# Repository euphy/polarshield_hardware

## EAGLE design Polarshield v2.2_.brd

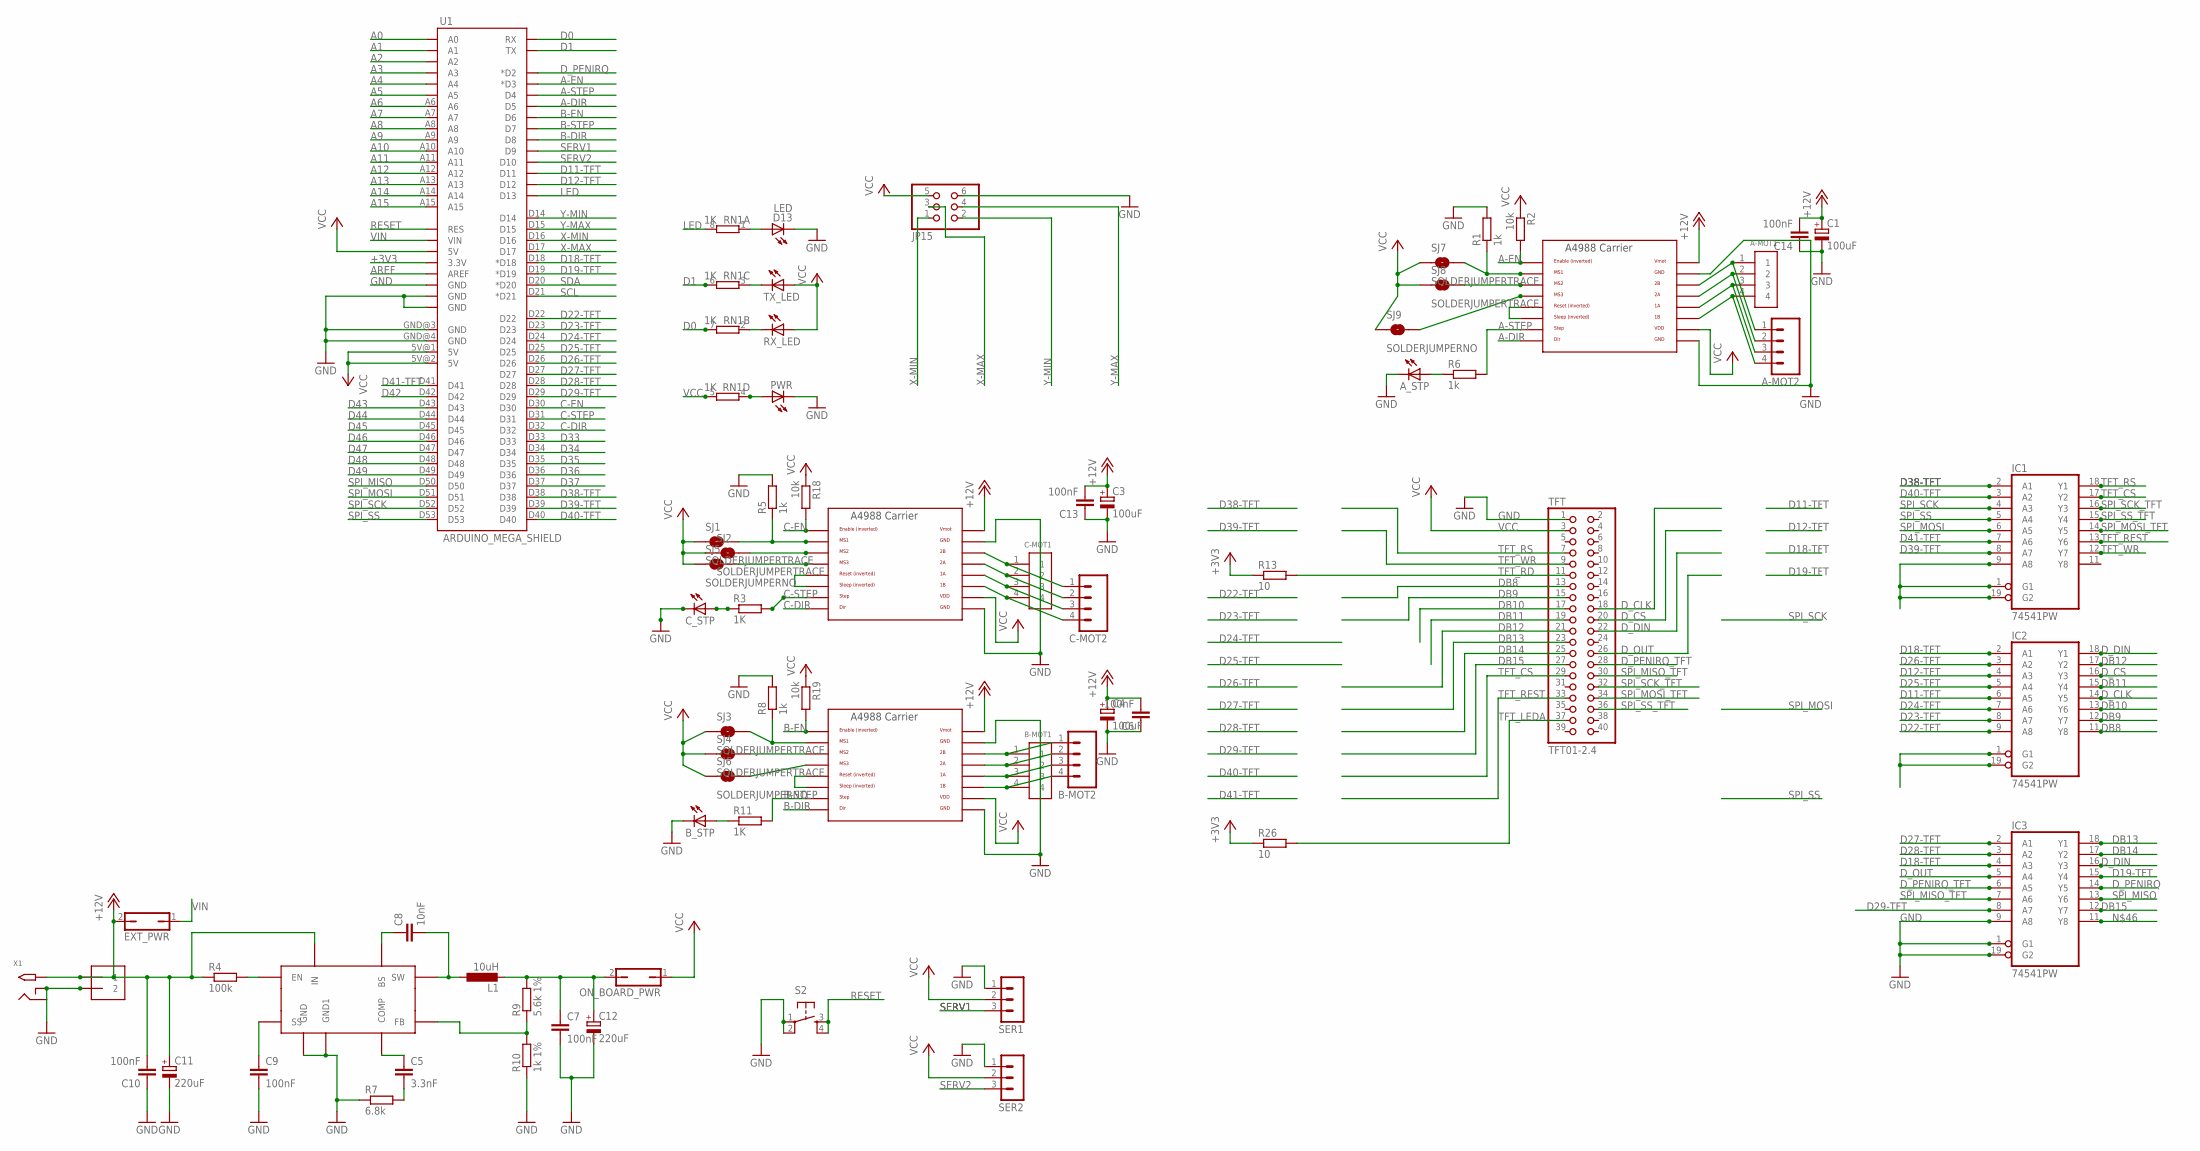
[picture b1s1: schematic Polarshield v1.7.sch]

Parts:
A-MOT1: 1X4-BIG; 1X04-BIG
A-MOT2: M04SCREW; SCREWTERMINAL-3.5MM-4
A_STP: LEDCHIP-LED0805; CHIP-LED0805
B-MOT1: 1X4-BIG; 1X04-BIG
B-MOT2: M04SCREW; SCREWTERMINAL-3.5MM-4
B_STP: LEDCHIP-LED0805; CHIP-LED0805
C1, C3, C4: 100uF; 153CLV-0605
C5: 3.3nF; C0805K
C6, C13, C14: 100nF; C0805
C7, C9, C10: 100nF; C0805K
C8: 10nF; C0805K
C11, C12: 220uF; 153CLV-0807
C-MOT1: 1X4-BIG; 1X04-BIG
C-MOT2: M04SCREW; SCREWTERMINAL-3.5MM-4
C_STP: LEDCHIP-LED0805; CHIP-LED0805
D13: LED; CHIP-LED0805
EXT_PWR: JP1Q; JP1
IC1, IC2, IC3: 74541PW; TSSOP20
IC4: MP2307; SOIC8
J1: 1X2-3.5MM
JP15: PINHD-2X3; 2X03
L1: 10uH; PIS2816
ON_BOARD_PWR: JP1Q; JP1
PWR: LEDCHIP-LED0805; CHIP-LED0805
R1, R5, R6, R8: 1k; R0805
R2, R18, R19: 10k; R0805
R3, R11: 1K; R0805
R4: 100k; R0805
R7: 6.8k; R0805
R9: 5.6k 1%; R0805
R10: 1k 1%; R0805
R13, R26: 10; R0805
RN1: 1K; EXBS8V
RX_LED: LEDCHIP-LED0805; CHIP-LED0805
S2: TAC_SWITCHPTH; TACTILE-PTH
SER1, SER2: 3PIN-HEADER
SJ1, SJ2, SJ3, SJ4, SJ7, SJ8: SOLDERJUMPERTRACE; SJ_2S-TRACE
SJ5, SJ6, SJ9: SOLDERJUMPERNO; SJ_2S-NO
TFT: TFT01-2.4
TX_LED: LEDCHIP-LED0805; CHIP-LED0805
U1: ARDUINO_MEGA_SHIELD
U$1, U$6, U$7: A4988BREAKOUT
X1: 2.1MMJACKTHM; PJ-102A

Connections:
+12V: C1.+, C3.+, C4.+, C6.2, C10.2, C11.+, C13.2, C14.2, EXT_PWR.2, IC4.IN, J1.1, R4.1, U$1.VMOT, U$6.VMOT, U$7.VMOT, X1.TIP; also elsewhere on the board
A0: U1.A0; also elsewhere on the board
A1: U1.A1; also elsewhere on the board
A2: U1.A2; also elsewhere on the board
A3: U1.A3; also elsewhere on the board
A4: U1.A4; also elsewhere on the board
A5: U1.A5; also elsewhere on the board
A6: U1.A6; also elsewhere on the board
A7: U1.A7; also elsewhere on the board
A8: U1.A8; also elsewhere on the board
A9: U1.A9; also elsewhere on the board
A10: U1.A10; also elsewhere on the board
A11: U1.A11; also elsewhere on the board
A12: U1.A12; also elsewhere on the board
A13: U1.A13; also elsewhere on the board
A14: U1.A14; also elsewhere on the board
A15: U1.A15; also elsewhere on the board
A-DIR: U1.D5, U$1.DIR
A-EN: R2.2, U1.D3 (*D3), U$1.EN
A-STEP: R6.2, U1.D4, U$1.STEP
AREF: U1.AREF
B-DIR: U1.D8, U$7.DIR
B-EN: R19.2, U1.D6, U$7.EN
B-STEP: R11.2, U1.D7, U$7.STEP
C-DIR: U1.D32, U$6.DIR
C-EN: R18.2, U1.D30, U$6.EN
C-STEP: R3.2, U1.D31, U$6.STEP
D0: RN1.7 (2), U1.RX
D1: RN1.6 (2), U1.TX
D11-TFT: IC2.6 (A5), U1.D11
D12-TFT: IC2.4 (A3), U1.D12
D19-TFT: IC3.15 (Y4), U1.D19 (*D19); also elsewhere on the board
D22-TFT: IC2.9 (A8), U1.D22
D23-TFT: IC2.8 (A7), U1.D23
D24-TFT: IC2.7 (A6), U1.D24
D25-TFT: IC2.5 (A4), U1.D25
D26-TFT: IC2.3 (A2), U1.D26
D27-TFT: IC3.2 (A1), U1.D27
D28-TFT: IC3.3 (A2), U1.D28
D29-TFT: IC3.8 (A7), U1.D29
D33: U1.D33; also elsewhere on the board
D34: U1.D34; also elsewhere on the board
D35: U1.D35; also elsewhere on the board
D36: U1.D36; also elsewhere on the board
D37: U1.D37; also elsewhere on the board
D38-TFT: IC1.2 (A1), U1.D38; also elsewhere on the board
D39-TFT: IC1.8 (A7), U1.D39; also elsewhere on the board
D40-TFT: IC1.3 (A2), U1.D40; also elsewhere on the board
D41-TFT: IC1.7 (A6), U1.D41; also elsewhere on the board
D42: U1.D42; also elsewhere on the board
D43: U1.D43; also elsewhere on the board
D44: U1.D44; also elsewhere on the board
D45: U1.D45; also elsewhere on the board
D46: U1.D46; also elsewhere on the board
D47: U1.D47; also elsewhere on the board
D48: U1.D48; also elsewhere on the board
D49: U1.D49; also elsewhere on the board
DB8: IC2.11 (Y8), TFT.13
DB9: IC2.12 (Y7), TFT.15
DB10: IC2.13 (Y6), TFT.17
DB11: IC2.15 (Y4), TFT.19
DB12: IC2.17 (Y2), TFT.21
DB13: IC3.18 (Y1), TFT.23
DB14: IC3.17 (Y2), TFT.25
DB15: IC3.12 (Y7), TFT.27
D_CLK: IC2.14 (Y5), TFT.18
D_CS: IC2.16 (Y3), TFT.20
D_DIN: IC2.18 (Y1), IC3.16 (Y3), TFT.22; also elsewhere on the board
D_PENIRQ: IC3.14 (Y5), U1.D2 (*D2); also elsewhere on the board
LED: RN1.8 (2), U1.D13
unnamed: U$6.RST, U$6.SLP (SLEEP)
unnamed: PWR.A, RN1.4 (1)
unnamed: R5.1, SJ1.2, U$6.MS1
unnamed: A-MOT1.1, A-MOT2.1, U$1.2B
unnamed: A-MOT1.2, A-MOT2.2, U$1.2A
unnamed: A-MOT1.3, A-MOT2.3, U$1.1A
unnamed: A-MOT1.4, A-MOT2.4, U$1.1B
unnamed: U$1.RST, U$1.SLP (SLEEP)
unnamed: R1.1, SJ7.2, U$1.MS1
unnamed: SJ2.2, U$6.MS2
unnamed: SJ8.2, U$1.MS2
unnamed: SJ5.2, U$6.MS3
unnamed: U$7.RST, U$7.SLP (SLEEP)
unnamed: SJ9.2, U$1.MS3
unnamed: RN1.2 (1), RX_LED.C
unnamed: RN1.3 (1), TX_LED.C
unnamed: SJ4.2, U$7.MS2
unnamed: B_STP.A, R11.1
unnamed: A_STP.A, R6.1
unnamed: D13.A, RN1.1
unnamed: C-MOT1.1, C-MOT2.1, U$6.2B
unnamed: C-MOT1.2, C-MOT2.2, U$6.2A
unnamed: C_STP.A, R3.1
unnamed: C-MOT1.3, C-MOT2.3, U$6.1A
unnamed: C-MOT1.4, C-MOT2.4, U$6.1B
unnamed: B-MOT1.1, B-MOT2.1, U$7.2B
unnamed: B-MOT1.2, B-MOT2.2, U$7.2A
unnamed: B-MOT1.3, B-MOT2.3, U$7.1A
unnamed: SJ6.2, U$7.MS3
unnamed 100: IC4.FB, R9.1, R10.2; also elsewhere on the board
unnamed: R8.1, SJ3.2, U$7.MS1
unnamed 102: IC4.EN, R4.2; also elsewhere on the board
unnamed: B-MOT1.4, B-MOT2.4, U$7.1B
unnamed 105: C9.1, IC4.SS; also elsewhere on the board
unnamed: C5.2, R7.2
unnamed 107: C5.1, IC4.COMP; also elsewhere on the board
unnamed 108: C8.1, IC4.BS; also elsewhere on the board
unnamed 109: C8.2, IC4.SW, L1.1; also elsewhere on the board
RESET: S2.3, S2.4, U1.RES
SCL: U1.D21 (*D21); also elsewhere on the board
SDA: U1.D20 (*D20); also elsewhere on the board
SERV1: SER1.3, U1.D9
SERV2: SER2.3, U1.D10
SPI_MISO: IC3.13 (Y6), U1.D50; also elsewhere on the board
SPI_MOSI: IC1.6 (A5), U1.D51; also elsewhere on the board
SPI_MOSI_TFT: IC1.14 (Y5), TFT.34; also elsewhere on the board
SPI_SCK: IC1.4 (A3), U1.D52; also elsewhere on the board
SPI_SCK_TFT: IC1.16 (Y3), TFT.32; also elsewhere on the board
SPI_SS: IC1.5 (A4), U1.D53; also elsewhere on the board
SPI_SS_TFT: IC1.15 (Y4), TFT.36; also elsewhere on the board
TFT_CS: IC1.17 (Y2), TFT.29; also elsewhere on the board
TFT_LEDA: R26.2, TFT.37
TFT_RD: R13.2, TFT.11
TFT_REST: IC1.13 (Y6), TFT.33; also elsewhere on the board
TFT_RS: IC1.18 (Y1), TFT.7; also elsewhere on the board
TFT_WR: IC1.12 (Y7), TFT.9; also elsewhere on the board
VIN: EXT_PWR.1, U1.VIN
X-MAX: JP15.3, U1.D17; also elsewhere on the board
X-MIN: JP15.1, U1.D16; also elsewhere on the board
Y-MAX: JP15.4, U1.D15; also elsewhere on the board
Y-MIN: JP15.2, U1.D14; also elsewhere on the board

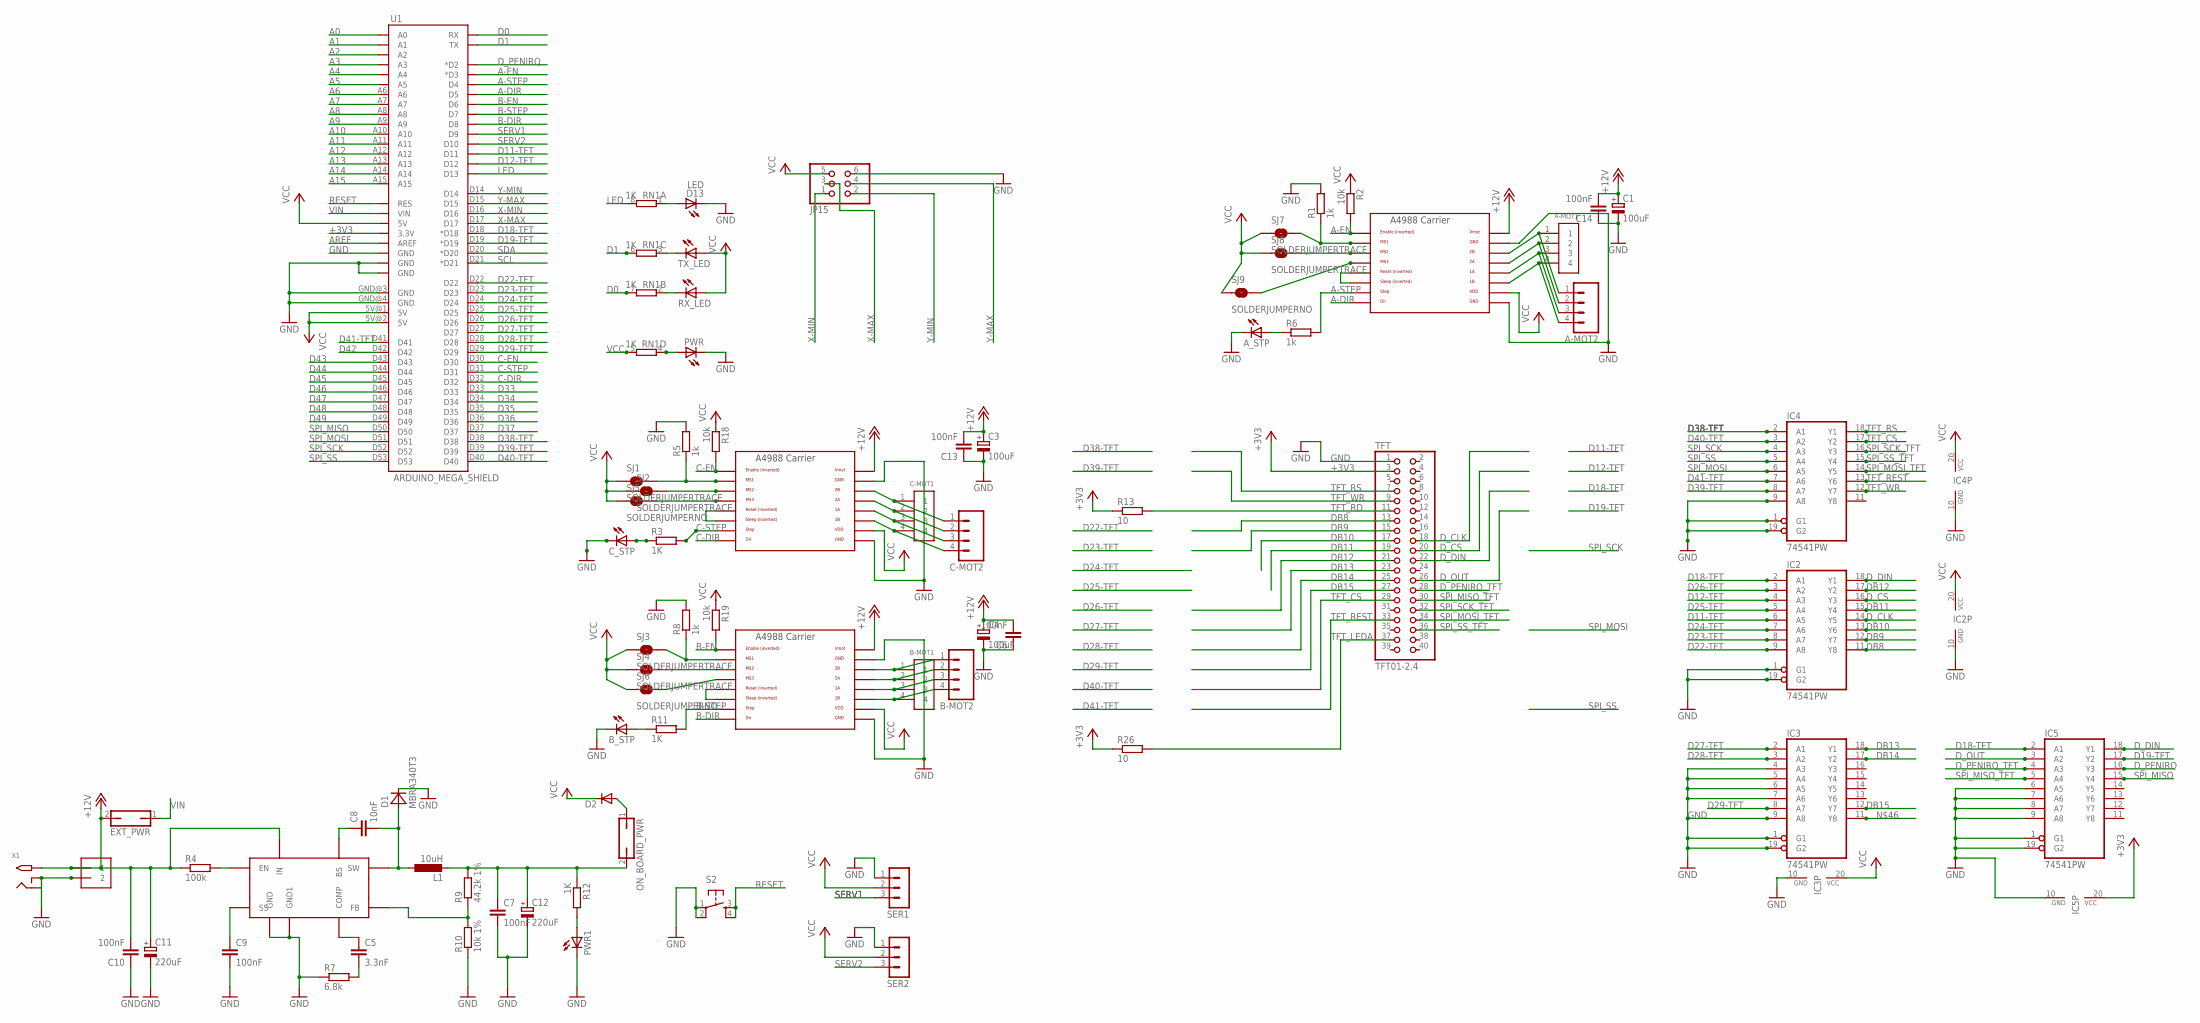
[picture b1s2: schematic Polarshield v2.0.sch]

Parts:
A-MOT1: 1X4-BIG; 1X04-BIG
A-MOT2: M04SCREW; SCREWTERMINAL-3.5MM-4
A_STP: LEDCHIP-LED0805; CHIP-LED0805
B-MOT1: 1X4-BIG; 1X04-BIG
B-MOT2: M04SCREW; SCREWTERMINAL-3.5MM-4
B_STP: LEDCHIP-LED0805; CHIP-LED0805
C1, C3, C4: 100uF; 153CLV-0605
C5: 3.3nF; C0805K
C6, C13, C14: 100nF; C0805
C7, C9, C10: 100nF; C0805K
C8: 10nF; C0805K
C11, C12: 220uF; 153CLV-0807
C-MOT1: 1X4-BIG; 1X04-BIG
C-MOT2: M04SCREW; SCREWTERMINAL-3.5MM-4
C_STP: LEDCHIP-LED0805; CHIP-LED0805
D1: MBRA340T3; SMA
D2: DIODE-DO214BA; DO214BA
D13: LED; CHIP-LED0805
EXT_PWR: JP1Q; JP1
IC1: MP2307; SOIC8
IC2, IC3, IC4, IC5: 74541PW; TSSOP20
J1: 1X2-3.5MM
JP15: PINHD-2X3; 2X03
L1: 10uH; PIS2816
ON_BOARD_PWR: JP1Q; JP1
PWR, PWR1: LEDCHIP-LED0805; CHIP-LED0805
R1, R5, R6, R8: 1k; R0805
R2, R18, R19: 10k; R0805
R3, R11, R12: 1K; R0805
R4: 100k; R0805
R7: 6.8k; R0805
R9: 44.2k 1%; R0805
R10: 10k 1%; R0805
R13, R26: 10; R0805
RN1: 1K; EXBS8V
RX_LED: LEDCHIP-LED0805; CHIP-LED0805
S2: TAC_SWITCHPTH; TACTILE-PTH
SER1, SER2: 3PIN-HEADER
SJ1, SJ2, SJ3, SJ4, SJ7, SJ8: SOLDERJUMPERTRACE; SJ_2S-TRACE
SJ5, SJ6, SJ9: SOLDERJUMPERNO; SJ_2S-NO
TFT: TFT01-2.4
TX_LED: LEDCHIP-LED0805; CHIP-LED0805
U1: ARDUINO_MEGA_SHIELD
U$1, U$6, U$7: A4988BREAKOUT
X1: 2.1MMJACKTHM; PJ-102A

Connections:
+12V: C1.+, C3.+, C4.+, C6.2, C10.2, C11.+, C13.2, C14.2, EXT_PWR.2, IC1.IN, J1.1, R4.1, U$1.VMOT, U$6.VMOT, U$7.VMOT, X1.TIP; also elsewhere on the board
A0: U1.A0; also elsewhere on the board
A1: U1.A1; also elsewhere on the board
A2: U1.A2; also elsewhere on the board
A3: U1.A3; also elsewhere on the board
A4: U1.A4; also elsewhere on the board
A5: U1.A5; also elsewhere on the board
A6: U1.A6; also elsewhere on the board
A7: U1.A7; also elsewhere on the board
A8: U1.A8; also elsewhere on the board
A9: U1.A9; also elsewhere on the board
A10: U1.A10; also elsewhere on the board
A11: U1.A11; also elsewhere on the board
A12: U1.A12; also elsewhere on the board
A13: U1.A13; also elsewhere on the board
A14: U1.A14; also elsewhere on the board
A15: U1.A15; also elsewhere on the board
A-DIR: U1.D5, U$1.DIR
A-EN: R2.2, U1.D3 (*D3), U$1.EN
A-STEP: R6.2, U1.D4, U$1.STEP
AREF: U1.AREF
B-DIR: U1.D8, U$7.DIR
B-EN: R19.2, U1.D6, U$7.EN
B-STEP: R11.2, U1.D7, U$7.STEP
C-DIR: U1.D32, U$6.DIR
C-EN: R18.2, U1.D30, U$6.EN
C-STEP: R3.2, U1.D31, U$6.STEP
D0: RN1.7 (2), U1.RX
D1: RN1.6 (2), U1.TX
D11-TFT: IC2.6 (A5), U1.D11
D12-TFT: IC2.4 (A3), U1.D12
D19-TFT: IC5.17 (Y2), U1.D19 (*D19); also elsewhere on the board
D22-TFT: IC2.9 (A8), U1.D22
D23-TFT: IC2.8 (A7), U1.D23
D24-TFT: IC2.7 (A6), U1.D24
D25-TFT: IC2.5 (A4), U1.D25
D26-TFT: IC2.3 (A2), U1.D26
D27-TFT: IC3.2 (A1), U1.D27
D28-TFT: IC3.3 (A2), U1.D28
D29-TFT: IC3.8 (A7), U1.D29
D33: U1.D33; also elsewhere on the board
D34: U1.D34; also elsewhere on the board
D35: U1.D35; also elsewhere on the board
D36: U1.D36; also elsewhere on the board
D37: U1.D37; also elsewhere on the board
D38-TFT: IC4.2 (A1), U1.D38; also elsewhere on the board
D39-TFT: IC4.8 (A7), U1.D39; also elsewhere on the board
D40-TFT: IC4.3 (A2), U1.D40; also elsewhere on the board
D41-TFT: IC4.7 (A6), U1.D41; also elsewhere on the board
D42: U1.D42; also elsewhere on the board
D43: U1.D43; also elsewhere on the board
D44: U1.D44; also elsewhere on the board
D45: U1.D45; also elsewhere on the board
D46: U1.D46; also elsewhere on the board
D47: U1.D47; also elsewhere on the board
D48: U1.D48; also elsewhere on the board
D49: U1.D49; also elsewhere on the board
DB8: IC2.11 (Y8), TFT.13
DB9: IC2.12 (Y7), TFT.15
DB10: IC2.13 (Y6), TFT.17
DB11: IC2.15 (Y4), TFT.19
DB12: IC2.17 (Y2), TFT.21
DB13: IC3.18 (Y1), TFT.23
DB14: IC3.17 (Y2), TFT.25
DB15: IC3.12 (Y7), TFT.27
D_CLK: IC2.14 (Y5), TFT.18
D_CS: IC2.16 (Y3), TFT.20
D_DIN: IC2.18 (Y1), IC5.18 (Y1), TFT.22; also elsewhere on the board
D_PENIRQ: IC5.16 (Y3), U1.D2 (*D2); also elsewhere on the board
LED: RN1.8 (2), U1.D13
unnamed: U$6.RST, U$6.SLP (SLEEP)
unnamed: PWR.A, RN1.4 (1)
unnamed: R5.1, SJ1.2, U$6.MS1
unnamed: A-MOT1.1, A-MOT2.1, U$1.2B
unnamed: A-MOT1.2, A-MOT2.2, U$1.2A
unnamed: A-MOT1.3, A-MOT2.3, U$1.1A
unnamed: A-MOT1.4, A-MOT2.4, U$1.1B
unnamed: U$1.RST, U$1.SLP (SLEEP)
unnamed: R1.1, SJ7.2, U$1.MS1
unnamed: SJ2.2, U$6.MS2
unnamed: SJ8.2, U$1.MS2
unnamed: SJ5.2, U$6.MS3
unnamed: U$7.RST, U$7.SLP (SLEEP)
unnamed: SJ9.2, U$1.MS3
unnamed: RN1.2 (1), RX_LED.C
unnamed: RN1.3 (1), TX_LED.C
unnamed: SJ4.2, U$7.MS2
unnamed: B_STP.A, R11.1
unnamed: A_STP.A, R6.1
unnamed: D13.A, RN1.1
unnamed: C-MOT1.1, C-MOT2.1, U$6.2B
unnamed: C-MOT1.2, C-MOT2.2, U$6.2A
unnamed: C_STP.A, R3.1
unnamed: PWR1.A, R12.2
unnamed: C-MOT1.3, C-MOT2.3, U$6.1A
unnamed: C-MOT1.4, C-MOT2.4, U$6.1B
unnamed: B-MOT1.1, B-MOT2.1, U$7.2B
unnamed: B-MOT1.2, B-MOT2.2, U$7.2A
unnamed: B-MOT1.3, B-MOT2.3, U$7.1A
unnamed: SJ6.2, U$7.MS3
unnamed 100: IC1.FB, R9.1, R10.2; also elsewhere on the board
unnamed: R8.1, SJ3.2, U$7.MS1
unnamed 102: IC1.EN, R4.2; also elsewhere on the board
unnamed: B-MOT1.4, B-MOT2.4, U$7.1B
unnamed 105: C9.1, IC1.SS; also elsewhere on the board
unnamed: C5.2, R7.2
unnamed 107: C5.1, IC1.COMP; also elsewhere on the board
unnamed 108: C8.1, IC1.BS; also elsewhere on the board
unnamed 109: C8.2, D1.A, IC1.SW, L1.1; also elsewhere on the board
RESET: S2.3, S2.4, U1.RES
SCL: U1.D21 (*D21); also elsewhere on the board
SDA: U1.D20 (*D20); also elsewhere on the board
SERV1: SER1.3, U1.D9
SERV2: SER2.3, U1.D10
SPI_MISO: IC5.15 (Y4), U1.D50; also elsewhere on the board
SPI_MOSI: IC4.6 (A5), U1.D51; also elsewhere on the board
SPI_MOSI_TFT: IC4.14 (Y5), TFT.34; also elsewhere on the board
SPI_SCK: IC4.4 (A3), U1.D52; also elsewhere on the board
SPI_SCK_TFT: IC4.16 (Y3), TFT.32; also elsewhere on the board
SPI_SS: IC4.5 (A4), U1.D53; also elsewhere on the board
SPI_SS_TFT: IC4.15 (Y4), TFT.36; also elsewhere on the board
TFT_CS: IC4.17 (Y2), TFT.29; also elsewhere on the board
TFT_LEDA: R26.2, TFT.37
TFT_RD: R13.2, TFT.11
TFT_REST: IC4.13 (Y6), TFT.33; also elsewhere on the board
TFT_RS: IC4.18 (Y1), TFT.7; also elsewhere on the board
TFT_WR: IC4.12 (Y7), TFT.9; also elsewhere on the board
VIN: EXT_PWR.1, U1.VIN
X-MAX: JP15.3, U1.D17; also elsewhere on the board
X-MIN: JP15.1, U1.D16; also elsewhere on the board
Y-MAX: JP15.4, U1.D15; also elsewhere on the board
Y-MIN: JP15.2, U1.D14; also elsewhere on the board

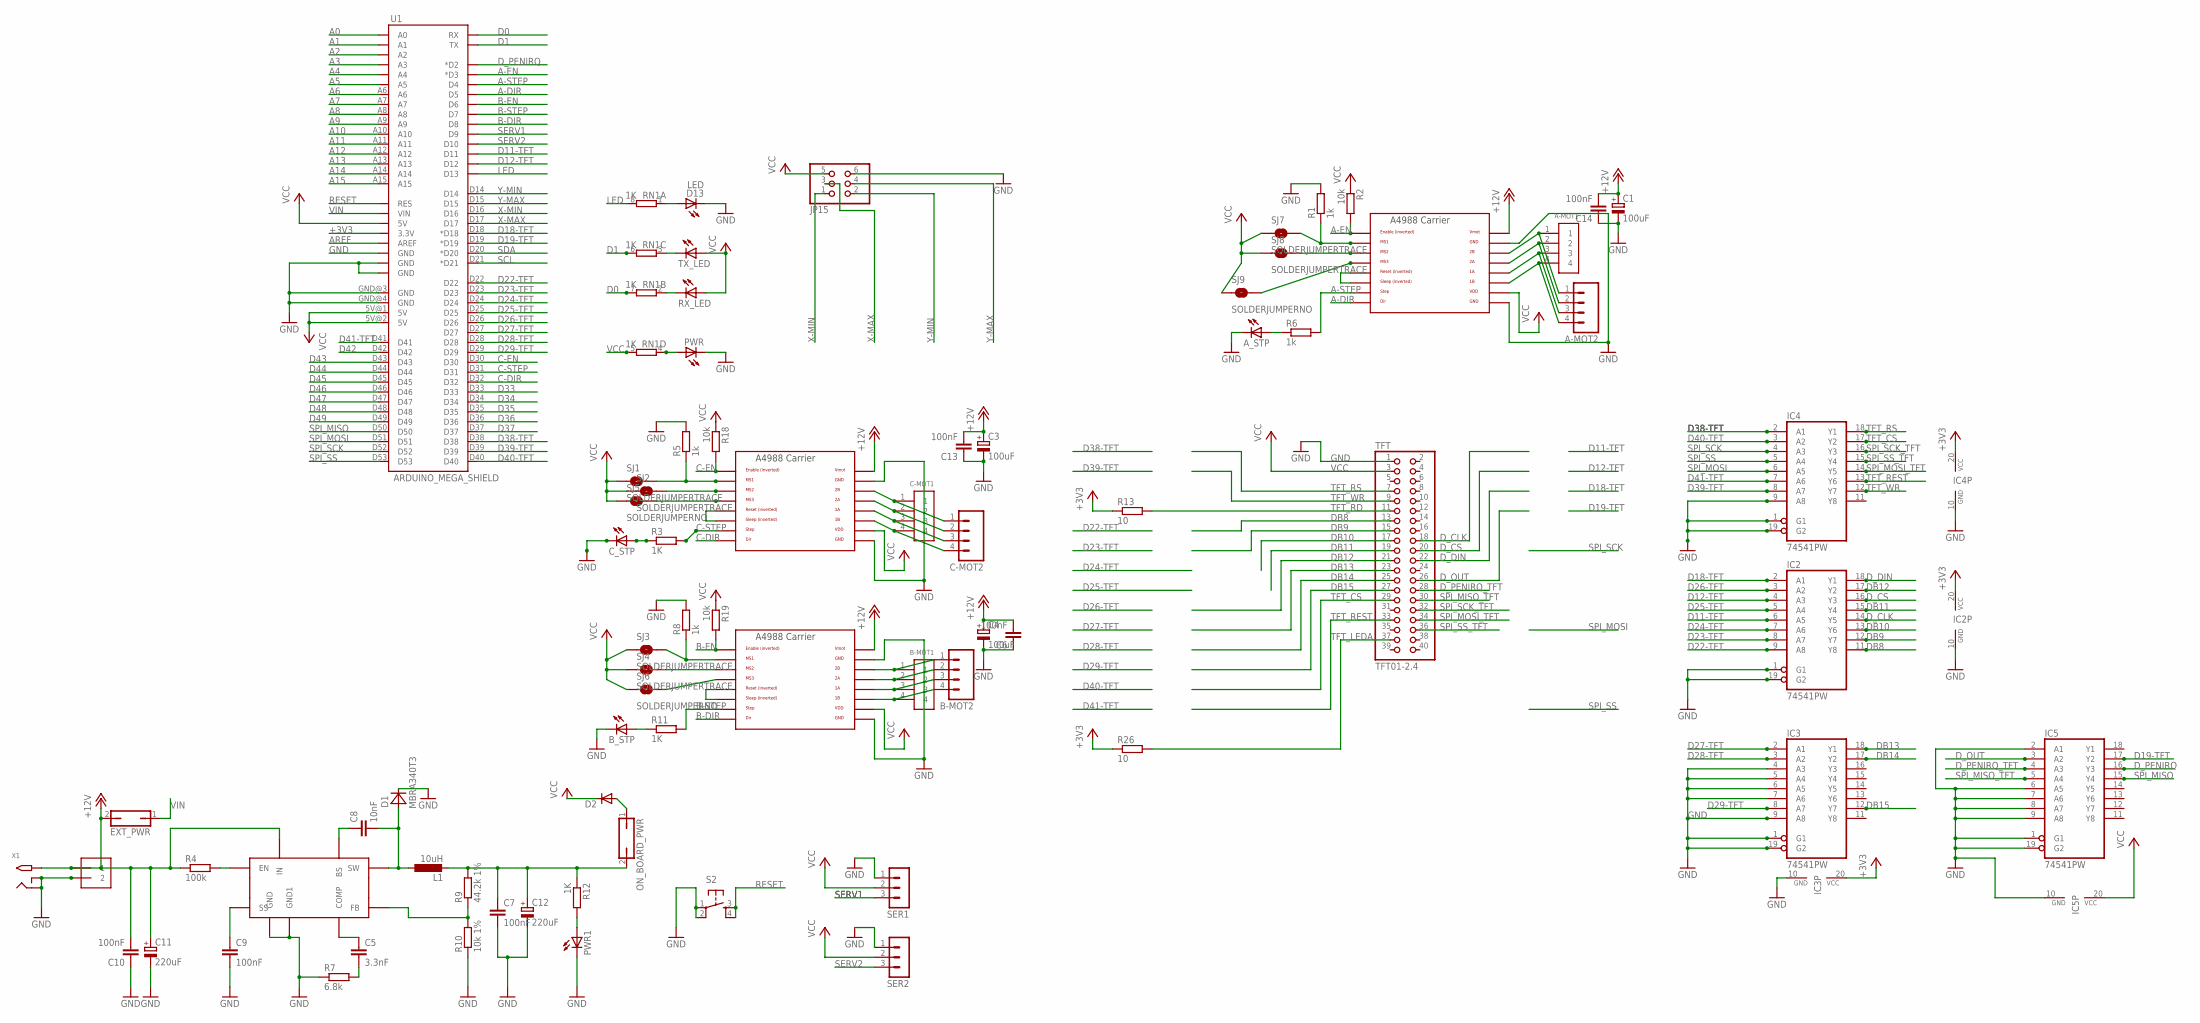
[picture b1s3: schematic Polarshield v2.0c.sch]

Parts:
A-MOT1: 1X4-BIG; 1X04-BIG
A-MOT2: M04SCREW; SCREWTERMINAL-3.5MM-4
A_STP: LEDCHIP-LED0805; CHIP-LED0805
B-MOT1: 1X4-BIG; 1X04-BIG
B-MOT2: M04SCREW; SCREWTERMINAL-3.5MM-4
B_STP: LEDCHIP-LED0805; CHIP-LED0805
C1, C3, C4: 100uF; 153CLV-0605
C5: 3.3nF; C0805K
C6, C13, C14: 100nF; C0805
C7, C9, C10: 100nF; C0805K
C8: 10nF; C0805K
C11, C12: 220uF; 153CLV-0807
C-MOT1: 1X4-BIG; 1X04-BIG
C-MOT2: M04SCREW; SCREWTERMINAL-3.5MM-4
C_STP: LEDCHIP-LED0805; CHIP-LED0805
D1: MBRA340T3; SMA
D2: DIODE-DO214BA; DO214BA
D13: LED; CHIP-LED0805
EXT_PWR: JP1Q; JP1
IC1: MP2307; SOIC8
IC2, IC3, IC4, IC5: 74541PW; TSSOP20
J1: 1X2-3.5MM
JP15: PINHD-2X3; 2X03
L1: 10uH; PIS2816
ON_BOARD_PWR: JP1Q; JP1
PWR, PWR1: LEDCHIP-LED0805; CHIP-LED0805
R1, R5, R6, R8: 1k; R0805
R2, R18, R19: 10k; R0805
R3, R11, R12: 1K; R0805
R4: 100k; R0805
R7: 6.8k; R0805
R9: 44.2k 1%; R0805
R10: 10k 1%; R0805
R13, R26: 10; R0805
RN1: 1K; EXBS8V
RX_LED: LEDCHIP-LED0805; CHIP-LED0805
S2: TAC_SWITCHPTH; TACTILE-PTH
SER1, SER2: 3PIN-HEADER
SJ1, SJ2, SJ3, SJ4, SJ7, SJ8: SOLDERJUMPERTRACE; SJ_2S-TRACE
SJ5, SJ6, SJ9: SOLDERJUMPERNO; SJ_2S-NO
TFT: TFT01-2.4
TX_LED: LEDCHIP-LED0805; CHIP-LED0805
U1: ARDUINO_MEGA_SHIELD
U$1, U$6, U$7: A4988BREAKOUT
X1: 2.1MMJACKTHM; PJ-102A

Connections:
+12V: C1.+, C3.+, C4.+, C6.2, C10.2, C11.+, C13.2, C14.2, EXT_PWR.2, IC1.IN, J1.1, R4.1, U$1.VMOT, U$6.VMOT, U$7.VMOT, X1.TIP; also elsewhere on the board
A0: U1.A0; also elsewhere on the board
A1: U1.A1; also elsewhere on the board
A2: U1.A2; also elsewhere on the board
A3: U1.A3; also elsewhere on the board
A4: U1.A4; also elsewhere on the board
A5: U1.A5; also elsewhere on the board
A6: U1.A6; also elsewhere on the board
A7: U1.A7; also elsewhere on the board
A8: U1.A8; also elsewhere on the board
A9: U1.A9; also elsewhere on the board
A10: U1.A10; also elsewhere on the board
A11: U1.A11; also elsewhere on the board
A12: U1.A12; also elsewhere on the board
A13: U1.A13; also elsewhere on the board
A14: U1.A14; also elsewhere on the board
A15: U1.A15; also elsewhere on the board
A-DIR: U1.D5, U$1.DIR
A-EN: R2.2, U1.D3 (*D3), U$1.EN
A-STEP: R6.2, U1.D4, U$1.STEP
AREF: U1.AREF
B-DIR: U1.D8, U$7.DIR
B-EN: R19.2, U1.D6, U$7.EN
B-STEP: R11.2, U1.D7, U$7.STEP
C-DIR: U1.D32, U$6.DIR
C-EN: R18.2, U1.D30, U$6.EN
C-STEP: R3.2, U1.D31, U$6.STEP
D0: RN1.7 (2), U1.RX
D1: RN1.6 (2), U1.TX
D11-TFT: IC2.6 (A5), U1.D11
D12-TFT: IC2.4 (A3), U1.D12
D19-TFT: IC5.17 (Y2), U1.D19 (*D19); also elsewhere on the board
D22-TFT: IC2.9 (A8), U1.D22
D23-TFT: IC2.8 (A7), U1.D23
D24-TFT: IC2.7 (A6), U1.D24
D25-TFT: IC2.5 (A4), U1.D25
D26-TFT: IC2.3 (A2), U1.D26
D27-TFT: IC3.2 (A1), U1.D27
D28-TFT: IC3.3 (A2), U1.D28
D29-TFT: IC3.8 (A7), U1.D29
D33: U1.D33; also elsewhere on the board
D34: U1.D34; also elsewhere on the board
D35: U1.D35; also elsewhere on the board
D36: U1.D36; also elsewhere on the board
D37: U1.D37; also elsewhere on the board
D38-TFT: IC4.2 (A1), U1.D38; also elsewhere on the board
D39-TFT: IC4.8 (A7), U1.D39; also elsewhere on the board
D40-TFT: IC4.3 (A2), U1.D40; also elsewhere on the board
D41-TFT: IC4.7 (A6), U1.D41; also elsewhere on the board
D42: U1.D42; also elsewhere on the board
D43: U1.D43; also elsewhere on the board
D44: U1.D44; also elsewhere on the board
D45: U1.D45; also elsewhere on the board
D46: U1.D46; also elsewhere on the board
D47: U1.D47; also elsewhere on the board
D48: U1.D48; also elsewhere on the board
D49: U1.D49; also elsewhere on the board
DB8: IC2.11 (Y8), TFT.13
DB9: IC2.12 (Y7), TFT.15
DB10: IC2.13 (Y6), TFT.17
DB11: IC2.15 (Y4), TFT.19
DB12: IC2.17 (Y2), TFT.21
DB13: IC3.18 (Y1), TFT.23
DB14: IC3.17 (Y2), TFT.25
DB15: IC3.12 (Y7), TFT.27
D_CLK: IC2.14 (Y5), TFT.18
D_CS: IC2.16 (Y3), TFT.20
D_DIN: IC2.18 (Y1), TFT.22; also elsewhere on the board
D_PENIRQ: IC5.16 (Y3), U1.D2 (*D2); also elsewhere on the board
LED: RN1.8 (2), U1.D13
unnamed: U$6.RST, U$6.SLP (SLEEP)
unnamed: PWR.A, RN1.4 (1)
unnamed: R5.1, SJ1.2, U$6.MS1
unnamed: A-MOT1.1, A-MOT2.1, U$1.2B
unnamed: A-MOT1.2, A-MOT2.2, U$1.2A
unnamed: A-MOT1.3, A-MOT2.3, U$1.1A
unnamed: A-MOT1.4, A-MOT2.4, U$1.1B
unnamed: U$1.RST, U$1.SLP (SLEEP)
unnamed: R1.1, SJ7.2, U$1.MS1
unnamed: SJ2.2, U$6.MS2
unnamed: SJ8.2, U$1.MS2
unnamed: SJ5.2, U$6.MS3
unnamed: U$7.RST, U$7.SLP (SLEEP)
unnamed: SJ9.2, U$1.MS3
unnamed: RN1.2 (1), RX_LED.C
unnamed: RN1.3 (1), TX_LED.C
unnamed: SJ4.2, U$7.MS2
unnamed: B_STP.A, R11.1
unnamed: A_STP.A, R6.1
unnamed: D13.A, RN1.1
unnamed: C-MOT1.1, C-MOT2.1, U$6.2B
unnamed: C-MOT1.2, C-MOT2.2, U$6.2A
unnamed: C_STP.A, R3.1
unnamed: PWR1.A, R12.2
unnamed: C-MOT1.3, C-MOT2.3, U$6.1A
unnamed: C-MOT1.4, C-MOT2.4, U$6.1B
unnamed: B-MOT1.1, B-MOT2.1, U$7.2B
unnamed: B-MOT1.2, B-MOT2.2, U$7.2A
unnamed: B-MOT1.3, B-MOT2.3, U$7.1A
unnamed: SJ6.2, U$7.MS3
unnamed 100: IC1.FB, R9.1, R10.2; also elsewhere on the board
unnamed: R8.1, SJ3.2, U$7.MS1
unnamed 102: IC1.EN, R4.2; also elsewhere on the board
unnamed: B-MOT1.4, B-MOT2.4, U$7.1B
unnamed 105: C9.1, IC1.SS; also elsewhere on the board
unnamed: C5.2, R7.2
unnamed 107: C5.1, IC1.COMP; also elsewhere on the board
unnamed 108: C8.1, IC1.BS; also elsewhere on the board
unnamed 109: C8.2, D1.A, IC1.SW, L1.1; also elsewhere on the board
RESET: S2.3, S2.4, U1.RES
SCL: U1.D21 (*D21); also elsewhere on the board
SDA: U1.D20 (*D20); also elsewhere on the board
SERV1: SER1.3, U1.D9
SERV2: SER2.3, U1.D10
SPI_MISO: IC5.15 (Y4), U1.D50; also elsewhere on the board
SPI_MOSI: IC4.6 (A5), U1.D51; also elsewhere on the board
SPI_MOSI_TFT: IC4.14 (Y5), TFT.34; also elsewhere on the board
SPI_SCK: IC4.4 (A3), U1.D52; also elsewhere on the board
SPI_SCK_TFT: IC4.16 (Y3), TFT.32; also elsewhere on the board
SPI_SS: IC4.5 (A4), U1.D53; also elsewhere on the board
SPI_SS_TFT: IC4.15 (Y4), TFT.36; also elsewhere on the board
TFT_CS: IC4.17 (Y2), TFT.29; also elsewhere on the board
TFT_LEDA: R26.2, TFT.37
TFT_RD: R13.2, TFT.11
TFT_REST: IC4.13 (Y6), TFT.33; also elsewhere on the board
TFT_RS: IC4.18 (Y1), TFT.7; also elsewhere on the board
TFT_WR: IC4.12 (Y7), TFT.9; also elsewhere on the board
VIN: EXT_PWR.1, U1.VIN
X-MAX: JP15.3, U1.D17; also elsewhere on the board
X-MIN: JP15.1, U1.D16; also elsewhere on the board
Y-MAX: JP15.4, U1.D15; also elsewhere on the board
Y-MIN: JP15.2, U1.D14; also elsewhere on the board

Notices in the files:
parts and their libraries:
SparkFun-Connectors: Licensing: Creative Commons ShareAlike 4.0 International - https://creativecommons.org/licenses/by-sa/4.0
